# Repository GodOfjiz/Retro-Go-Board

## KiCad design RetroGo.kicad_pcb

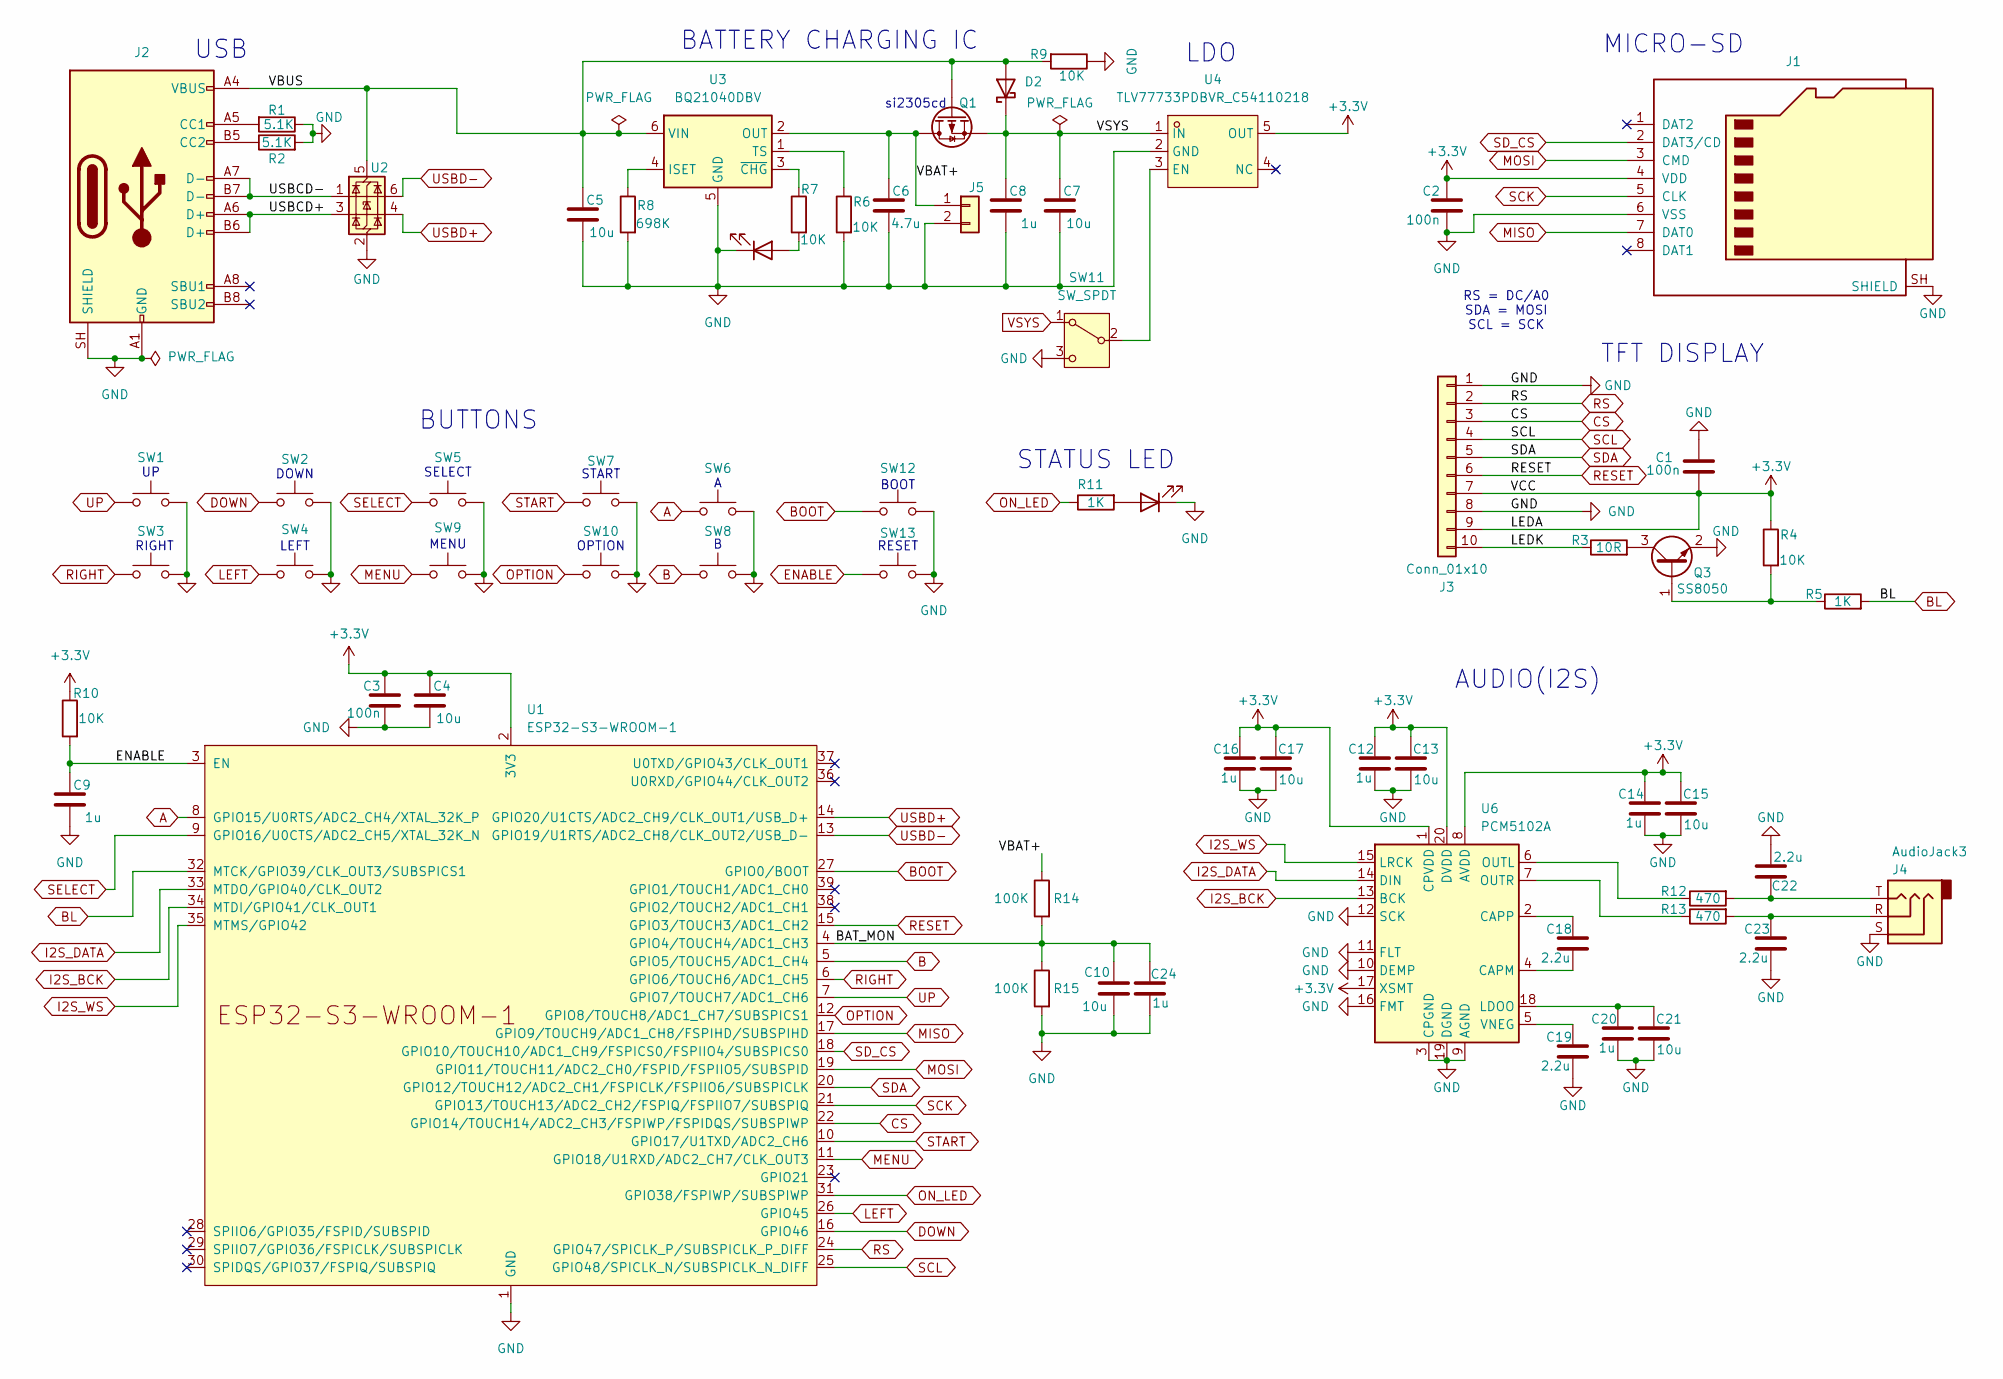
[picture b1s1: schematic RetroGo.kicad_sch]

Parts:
C1, C2, C3: 100n; C_0805_2012Metric_Pad1.18x1.45mm_HandSolder
C4, C5, C7, C10, C13, C15, C17, C21: 10u; C_0805_2012Metric_Pad1.18x1.45mm_HandSolder
C6: 4.7u; C_0805_2012Metric_Pad1.18x1.45mm_HandSolder
C8, C12, C14, C16, C20, C24: 1u; C_0805_2012Metric_Pad1.18x1.45mm_HandSolder
C9: 1u; C_0603_1608Metric_Pad1.08x0.95mm_HandSolder
C18, C19, C22, C23: 2.2u; C_0603_1608Metric_Pad1.08x0.95mm_HandSolder
D1, D3: LED; LED_0805_2012Metric_Pad1.15x1.40mm_HandSolder
D2: D_Schottky; D_SMA_Handsoldering
J1: Micro_SD_Card; microSD_HC_Hirose_DM3AT-SF-PEJM5
J2: USB_C_Receptacle_USB2.0_16P; USB_C_Receptacle_GCT_USB4105-xx-A_16P_TopMnt_Horizontal
J3: Conn_01x10; Hirose_FH12-10S-0.5SH_1x10-1MP_P0.50mm_Horizontal
J4: AudioJack3; Jack_3.5mm_CUI_SJ-3523-SMT_Horizontal
J5: Conn_01x02; JST_PH_B2B-PH-K_1x02_P2.00mm_Vertical
Q1: Q_PMOS; SOT-23_Handsoldering
Q3: SS8050; SOT-23
R1, R2: 5.1K; R_0603_1608Metric_Pad0.98x0.95mm_HandSolder
R3: 10R; R_0603_1608Metric_Pad0.98x0.95mm_HandSolder
R4, R6, R7, R9, R10: 10K; R_0603_1608Metric_Pad0.98x0.95mm_HandSolder
R5, R11: 1K; R_0603_1608Metric_Pad0.98x0.95mm_HandSolder
R8: 698K; R_0603_1608Metric_Pad0.98x0.95mm_HandSolder
R12, R13: 470; R_0603_1608Metric_Pad0.98x0.95mm_HandSolder
R14, R15: 100K; R_0603_1608Metric_Pad0.98x0.95mm_HandSolder
SW1, SW2, SW3, SW4, SW5, SW6, SW7, SW8, SW9, SW10, SW12, SW13: SW_Push; SW_Push_1P1T_NO_E-Switch_TL3301NxxxxxG
SW11: SW_SPDT; SW_Slide_SPDT_Angled_CK_OS102011MA1Q
U1: ESP32-S3-WROOM-1
U2: USBLC6-2SC6; SOT-23-6
U3: BQ21040DBV; SOT-23-6
U4: TLV77733PDBVR_C54110218; SOT-23-5_HandSoldering; MPN TLV77733PDBVR; LCSC Part C54110218
U6: PCM5102A; TSSOP-20_4.4x6.5mm_P0.65mm

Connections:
+3.3V: C1.1, C2.1, C3.2, C4.2, C12.2, C13.2, C14.2, C15.2, C16.2, C17.2, J1.4 (VDD), J3.7, J3.9, R4.1, R10.1, U1.2 (3V3), U4.5 (OUT), U6.1 (CPVDD), U6.8 (AVDD), U6.17 (XSMT), U6.20 (DVDD)
/BAT_MON: C10.2, C24.2, R14.2, R15.1, U1.4 (GPIO4/TOUCH4/ADC1_CH3)
/LEDK: J3.10, R3.1
/USBCD+: J2.A6 (D+), J2.B6 (D+), U2.3 (I/O2)
/USBCD-: J2.A7 (D-), J2.B7 (D-), U2.1 (I/O1)
/VBAT+: C6.2, J5.1, Q1.3 (D), R14.1, U3.2 (OUT)
/VBUS: C5.2, D2.2 (A), J2.A4 (VBUS), J2.A9 (VBUS), J2.B4 (VBUS), J2.B9 (VBUS), Q1.1 (G), R9.2, U2.5 (VBUS), U3.6 (VIN)
A: SW6.1, U1.8 (GPIO15/U0RTS/ADC2_CH4/XTAL_32K_P)
B: SW8.1, U1.5 (GPIO5/TOUCH5/ADC1_CH4)
BL: R5.2, U1.32 (MTCK/GPIO39/CLK_OUT3/SUBSPICS1)
BOOT: SW12.1, U1.27 (GPIO0/BOOT)
CS: J3.3, U1.22 (GPIO14/TOUCH14/ADC2_CH3/FSPIWP/FSPIDQS/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)
DOWN: SW2.1, U1.16 (GPIO46)
ENABLE: C9.2, R10.2, SW13.1, U1.3 (EN)
GND: C1.2, C2.2, C3.1, C4.1, C5.1, C6.1, C7.1, C8.1, C9.1, C10.1, C12.1, C13.1, C14.1, C15.1, C16.1, C17.1, C19.1, C20.1, C21.1, C22.1, C23.1, C24.1, D1.1 (K), D3.1 (K), J1.6 (VSS), J1.SH (SHIELD), J2.A1 (GND), J2.A12 (GND), J2.B1 (GND), J2.B12 (GND), J2.SH (SHIELD), J3.1, J3.8, J4.S, J5.2, Q3.2 (E), R1.1, R2.2, R6.2, R8.2, R9.1, R15.2, SW1.2, SW2.2, SW3.2, SW4.2, SW5.2, SW6.2, SW7.2, SW8.2, SW9.2, SW10.2, SW11.3 (C), SW12.2, SW13.2, U1.1 (GND), U1.40 (GND), U1.41 (GND), U2.2 (GND), U3.5 (GND), U4.2 (GND), U6.3 (CPGND), U6.9 (AGND), U6.10 (DEMP), U6.11 (FLT), U6.12 (SCK), U6.16 (FMT), U6.19 (DGND)
I2S_BCK: U1.34 (MTDI/GPIO41/CLK_OUT1), U6.13 (BCK)
I2S_DATA: U1.33 (MTDO/GPIO40/CLK_OUT2), U6.14 (DIN)
I2S_WS: U1.35 (MTMS/GPIO42), U6.15 (LRCK)
LEFT: SW4.1, U1.26 (GPIO45)
MENU: SW9.1, U1.11 (GPIO18/U1RXD/ADC2_CH7/CLK_OUT3)
MISO: J1.7 (DAT0), U1.17 (GPIO9/TOUCH9/ADC1_CH8/FSPIHD/SUBSPIHD)
MOSI: J1.3 (CMD), U1.19 (GPIO11/TOUCH11/ADC2_CH0/FSPID/FSPIIO5/S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)
unnamed: C22.2, J4.T, R12.2
unnamed: C23.2, J4.R, R13.2
unnamed: D1.2 (A), R7.2
unnamed: D3.2 (A), R11.2
unnamed: J2.A5 (CC1), R1.2
unnamed: J2.B5 (CC2), R2.1
unnamed: Q3.1 (B), R4.2, R5.1
unnamed: Q3.3 (C), R3.2
unnamed: SW11.2 (B), U4.3 (EN)
unnamed: R8.1, U3.4 (ISET)
unnamed: R6.1, U3.1 (TS)
unnamed: R7.1, U3.3 (~CHG)
unnamed: C18.1, U6.4 (CAPM)
unnamed: C18.2, U6.2 (CAPP)
unnamed: C20.2, C21.2, U6.18 (LDOO)
unnamed: R12.1, U6.6 (OUTL)
unnamed: R13.1, U6.7 (OUTR)
unnamed: C19.2, U6.5 (VNEG)
ON_LED: R11.1, U1.31 (GPIO38/FSPIWP/SUBSPIWP)
OPTION: SW10.1, U1.12 (GPIO8/TOUCH8/ADC1_CH7/SUBSPICS1)
RESET: J3.6, U1.15 (GPIO3/TOUCH3/ADC1_CH2)
RIGHT: SW3.1, U1.6 (GPIO6/TOUCH6/ADC1_CH5)
RS: J3.2, U1.24 (GPIO47/SPICLK_P/SUBSPICLK_P_DIFF)
SCK: J1.5 (CLK), U1.21 (GPIO13/TOUCH13/ADC2_CH2/FSPIQ/FSPIIO7/S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)
SCL: J3.4, U1.25 (GPIO48/SPICLK_N/SUBSPICLK_N_DIFF)
SDA: J3.5, U1.20 (GPIO12/TOUCH12/ADC2_CH1/FSPICLK/FSPIIO6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)
SD_CS: J1.2 (DAT3/CD), U1.18 (GPIO10/TOUCH10/ADC1_CH9/FSPICS0/FSPIIO4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)
SELECT: SW5.1, U1.9 (GPIO16/U0CTS/ADC2_CH5/XTAL_32K_N)
START: SW7.1, U1.10 (GPIO17/U1TXD/ADC2_CH6)
UP: SW1.1, U1.7 (GPIO7/TOUCH7/ADC1_CH6)
USBD+: U1.14 (GPIO20/U1CTS/ADC2_CH9/CLK_OUT1/USB_D+), U2.4 (I/O2)
USBD-: U1.13 (GPIO19/U1RTS/ADC2_CH8/CLK_OUT2/USB_D-), U2.6 (I/O1)
VSYS: C7.2, C8.2, D2.1 (K), Q1.2 (S), SW11.1 (A), U4.1 (IN)

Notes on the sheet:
TFT DISPLAY
si2305cd
MICRO-SD
BUTTONS
BOOT
AUDIO(I2S)
RESET
RIGHT
USB
BATTERY CHARGING IC
STATUS LED
OPTION
MENU
LDO
LEFT
SELECT
DOWN
START
RS = DC/A0 SDA = MOSI SCL = SCK

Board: 2 copper layers, 66 parts (4 on the bottom side), 55 nets, no tracks yet.
